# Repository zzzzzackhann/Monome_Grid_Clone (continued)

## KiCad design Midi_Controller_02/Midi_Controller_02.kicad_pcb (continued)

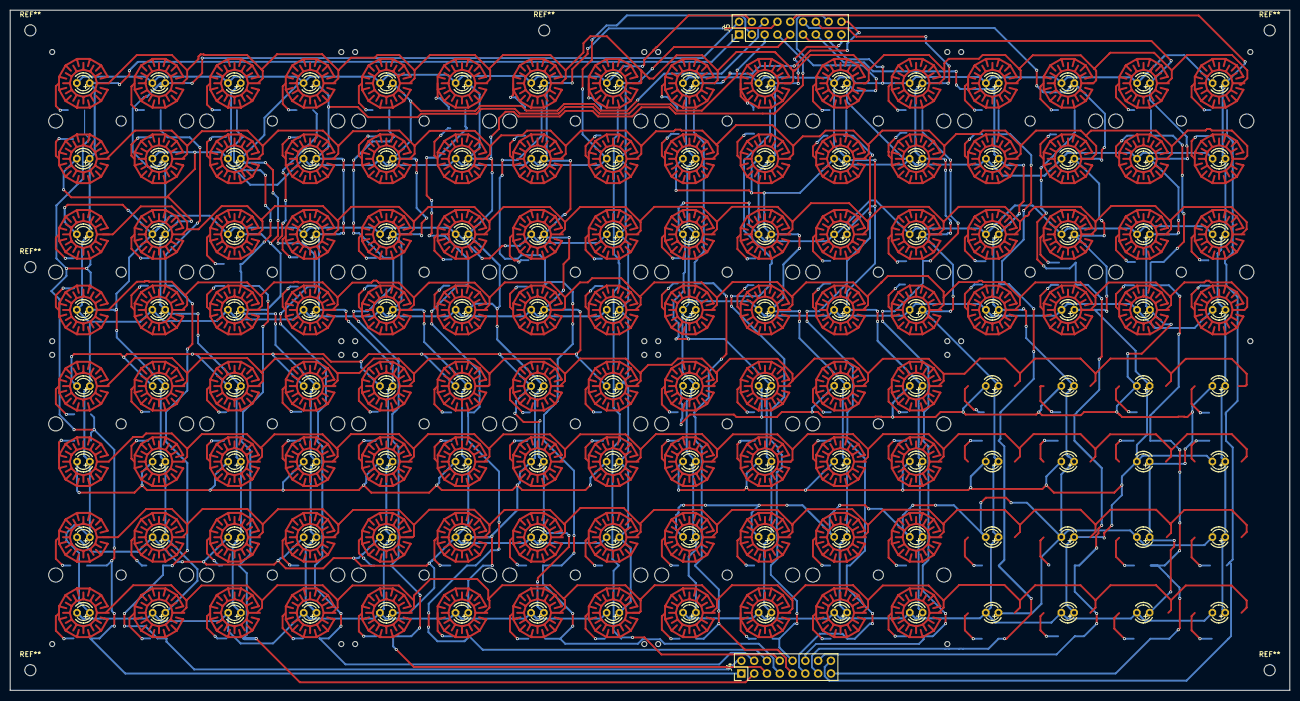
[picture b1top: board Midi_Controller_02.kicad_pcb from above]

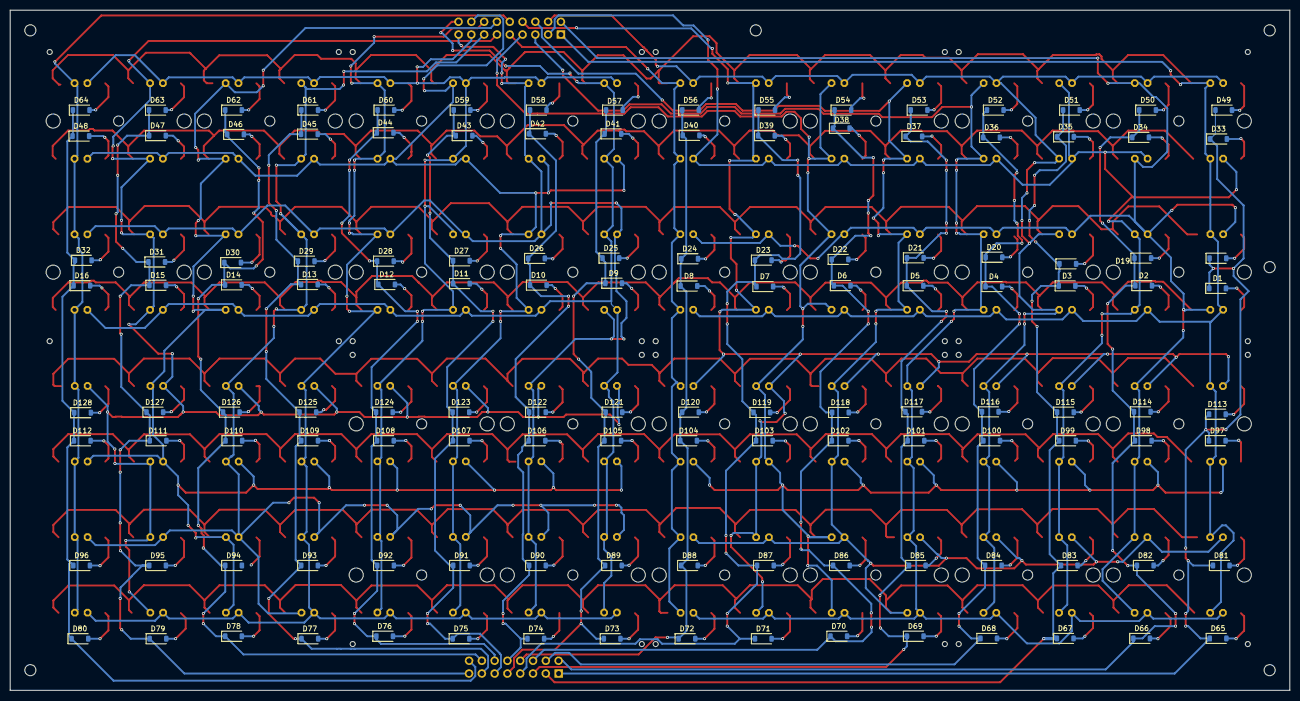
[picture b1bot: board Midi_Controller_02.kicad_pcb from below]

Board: 2 copper layers, 254.0 x 135.0 mm, 145 parts (128 on the bottom side), 154 nets.

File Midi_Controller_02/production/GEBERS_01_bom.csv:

Designator,Footprint,Quantity,Value,LCSC Part #
"D1, D10, D100, D101, D102, D103, D104, D105, D106, D107, D108, D109, D11, D110, D111, D112, D113, D114, D115, D116, D117, D118, D119, D12, D120, D121, D122, D123, D124, D125, D126, D127, D128, D13, D14, D15, D16, D17, D18, D19, D2, D20, D21, D22, D23, D24, D25, D26, D27, D28, D29, D3, D30, D31, D32, D33, D34, D35, D36, D37, D38, D39, D4, D40, D41, D42, D43, D44, D45, D46, D47, D48, D49, D5, D50, D51, D52, D53, D54, D55, D56, D57, D58, D59, D6, D60, D61, D62, D63, D64, D65, D66, D67, D68, D69, D7, D70, D71, D72, D73, D74, D75, D76, D77, D78, D79, D8, D80, D81, D82, D83, D84, D85, D86, D87, D88, D89, D9, D90, D91, D92, D93, D94, D95, D96, D97, D98, D99",D_SOD-123,128,1N4148,
J4,PinHeader_2x08_P2.54mm_Vertical,1,COL HEADER,
J5,PinHeader_2x09_P2.54mm_Vertical,1,CA HEADER,
"LED1, LED2, LED3, LED4, LED5, LED6, LED7, LED8",LED3MM-4X4GRID,8,~,
"SW2, SW3, SW4, SW5, SW6, SW7, SW8, SW9",ELAST_PAD_SQUARE_10MM_5.4MM_4X4GRID,8,~,

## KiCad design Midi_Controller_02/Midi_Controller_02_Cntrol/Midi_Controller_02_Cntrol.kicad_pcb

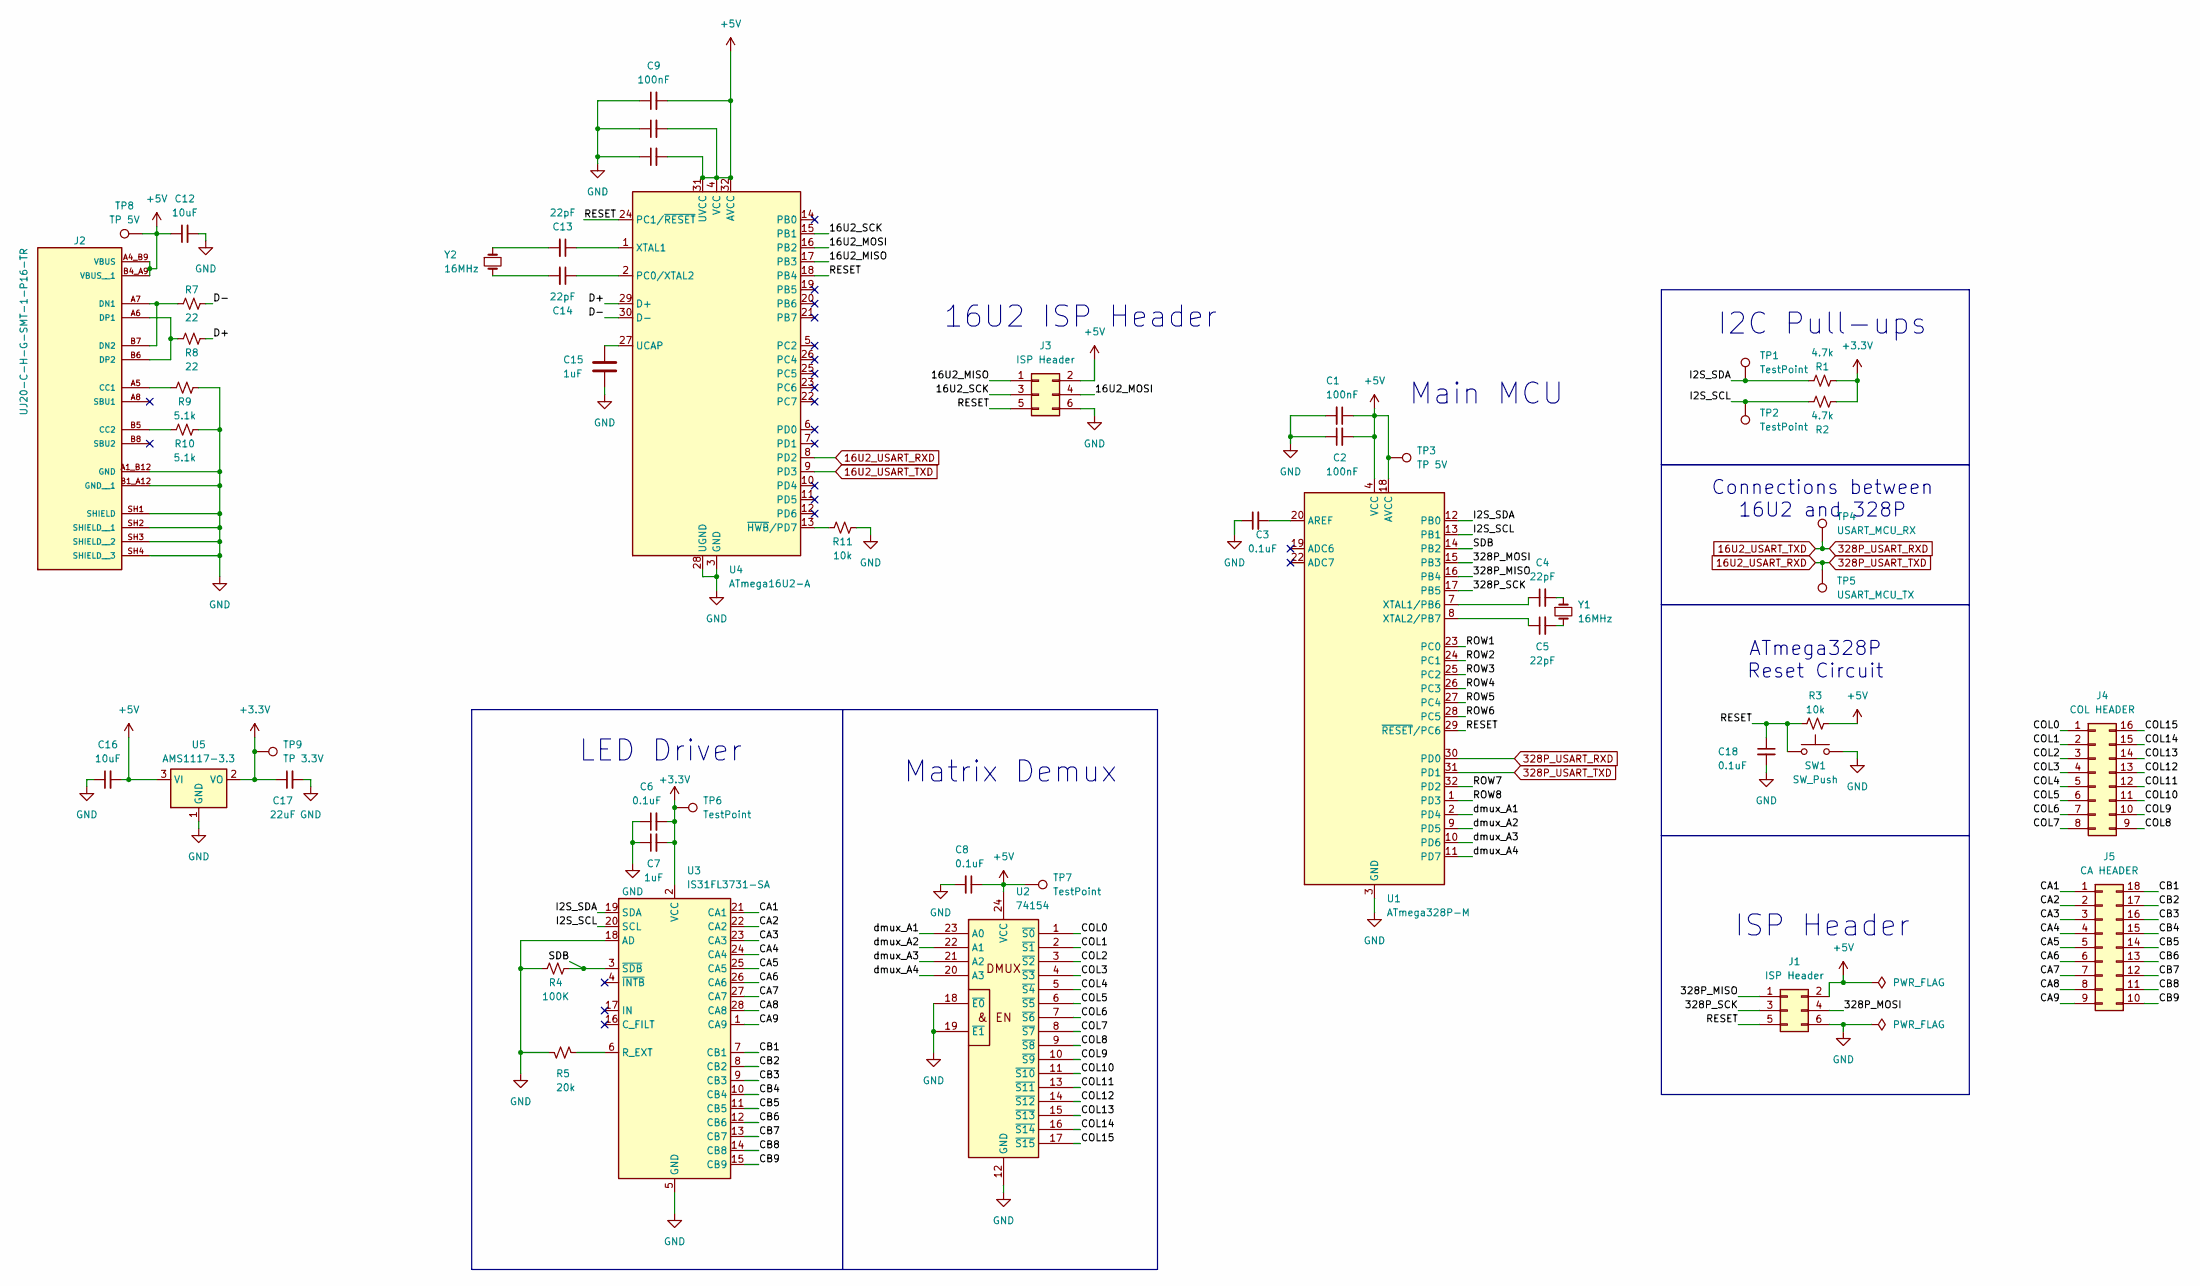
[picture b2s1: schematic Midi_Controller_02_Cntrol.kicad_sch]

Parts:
C1, C2, C9, C10, C11: 100nF; C_0805_2012Metric
C3, C6, C8, C18: 0.1uF; C_0805_2012Metric
C4, C5, C13, C14: 22pF; C_0805_2012Metric
C7, C15: 1uF; C_0805_2012Metric
C12, C16: 10uF; C_0805_2012Metric
C17: 22uF; C_0805_2012Metric
J1, J3: ISP Header; TestPoint_Pad_D1.0mm_2x3
J2: UJ20-C-H-G-SMT-1-P16-TR; SAMESKY_UJ20-C-H-G-SMT-1-P16-TR; PARTREV 1.0
J4: COL HEADER; PinHeader_2x08_P2.54mm_Horizontal
J5: CA HEADER; PinHeader_2x09_P2.54mm_Horizontal
R1, R2: 4.7k; R_0805_2012Metric
R3, R11: 10k; R_0805_2012Metric
R4: 100K; R_0805_2012Metric
R5: 20k; R_0805_2012Metric
R7, R8: 22; R_0805_2012Metric
R9, R10: 5.1k; R_0805_2012Metric
SW1: SW_Push; SW_TS04-66-55-BK-100-SMT
TP1, TP2: TestPoint; SolderWire-0.5sqmm_1x01_D0.9mm_OD2.3mm
TP3, TP8: TP 5V; TestPoint_Pad_D1.5mm
TP4: USART_MCU_RX; SolderWire-0.5sqmm_1x01_D0.9mm_OD2.3mm
TP5: USART_MCU_TX; SolderWire-0.5sqmm_1x01_D0.9mm_OD2.3mm
TP6, TP7: TestPoint; TestPoint_Pad_D1.5mm
TP9: TP 3.3V; TestPoint_Pad_D1.5mm
U1: ATmega328P-M; QFN-32-1EP_5x5mm_P0.5mm_EP3.1x3.1mm
U2: 74154; SOIC-24W_7.5x15.4mm_P1.27mm
U3: IS31FL3731-SA; SSOP-28_5.3x10.2mm_P0.65mm
U4: ATmega16U2-A; TQFP-32_7x7mm_P0.8mm
U5: AMS1117-3.3; SOT-223-3_TabPin2
Y1, Y2: 16MHz; Crystal_HC49-4H_Vertical

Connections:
16U2_USART_RXD: TP5.1 (1_1), U1.31 (PD1), U4.8 (PD2)
16U2_USART_TXD: TP4.1 (1_1), U1.30 (PD0), U4.9 (PD3)
+3.3V: C6.2, C7.2, C17.1, R1.1, R2.1, TP6.1 (1_1), TP9.1 (1_1), U3.2 (VCC), U5.2 (VO)
+5V: C1.1, C2.2, C8.1, C9.2, C10.2, C11.2, C12.1, C16.2, J1.2, J2.A4_B9 (VBUS), J2.B4_A9 (VBUS__1), J3.2, R3.2, TP3.1 (1_1), TP7.1 (1_1), TP8.1 (1_1), U1.4 (VCC), U1.6 (VCC), U1.18 (AVCC), U2.24 (VCC), U4.4 (VCC), U4.31 (UVCC), U4.32 (AVCC), U5.3 (VI)
/16U2_MISO: J3.1, U4.17 (PB3)
/16U2_MOSI: J3.4, U4.16 (PB2)
/16U2_SCK: J3.3, U4.15 (PB1)
/328P_MISO: J1.1, U1.16 (PB4)
/328P_MOSI: J1.4, U1.15 (PB3)
/328P_SCK: J1.3, U1.17 (PB5)
/CA1: J5.1, U3.21 (CA1)
/CA2: J5.2, U3.22 (CA2)
/CA3: J5.3, U3.23 (CA3)
/CA4: J5.4, U3.24 (CA4)
/CA5: J5.5, U3.25 (CA5)
/CA6: J5.6, U3.26 (CA6)
/CA7: J5.7, U3.27 (CA7)
/CA8: J5.8, U3.28 (CA8)
/CA9: J5.9, U3.1 (CA9)
/CB1: J5.18, U3.7 (CB1)
/CB2: J5.17, U3.8 (CB2)
/CB3: J5.16, U3.9 (CB3)
/CB4: J5.15, U3.10 (CB4)
/CB5: J5.14, U3.11 (CB5)
/CB6: J5.13, U3.12 (CB6)
/CB7: J5.12, U3.13 (CB7)
/CB8: J5.11, U3.14 (CB8)
/CB9: J5.10, U3.15 (CB9)
/COL0: J4.1, U2.1 (~S0)
/COL1: J4.2, U2.2 (~S1)
/COL2: J4.3, U2.3 (~S2)
/COL3: J4.4, U2.4 (~S3)
/COL4: J4.5, U2.5 (~S4)
/COL5: J4.6, U2.6 (~S5)
/COL6: J4.7, U2.7 (~S6)
/COL7: J4.8, U2.8 (~S7)
/COL8: J4.9, U2.9 (~S8)
/COL9: J4.10, U2.10 (~S9)
/COL10: J4.11, U2.11 (~S10)
/COL11: J4.12, U2.13 (~S11)
/COL12: J4.13, U2.14 (~S12)
/COL13: J4.14, U2.15 (~S13)
/COL14: J4.15, U2.16 (~S14)
/COL15: J4.16, U2.17 (~S15)
/D+: R8.1, U4.29 (D+)
/D-: R7.2, U4.30 (D-)
/I2S_SCL: R2.2, TP2.1 (1_1), U1.13 (PB1), U3.20 (SCL)
/I2S_SDA: R1.2, TP1.1 (1_1), U1.12 (PB0), U3.19 (SDA)
/RESET: C18.1, J1.5, J3.5, R3.1, SW1.1, U1.29 (~RESET/PC6), U4.18 (PB4), U4.24 (PC1/~RESET)
/ROW1: U1.23 (PC0)
/ROW2: U1.24 (PC1)
/ROW3: U1.25 (PC2)
/ROW4: U1.26 (PC3)
/ROW5: U1.27 (PC4)
/ROW6: U1.28 (PC5)
/ROW7: U1.32 (PD2)
/ROW8: U1.1 (PD3)
/SDB: R4.2, U1.14 (PB2), U3.3 (~SDB)
/dmux_A1: U1.2 (PD4), U2.23 (A0)
/dmux_A2: U1.9 (PD5), U2.22 (A1)
/dmux_A3: U1.10 (PD6), U2.21 (A2)
/dmux_A4: U1.11 (PD7), U2.20 (A3)
GND: C1.2, C2.1, C3.1, C6.1, C7.1, C8.2, C9.1, C10.1, C11.1, C12.2, C15.2, C16.1, C17.2, C18.2, J1.6, J2.A1_B12 (GND), J2.B1_A12 (GND__1), J2.SH1 (SHIELD), J2.SH2 (SHIELD__1), J2.SH3 (SHIELD__2), J2.SH4 (SHIELD__3), J3.6, R4.1, R5.1, R9.2, R10.1, R11.1, SW1.2, U1.3 (GND), U1.5 (GND), U1.21 (GND), U1.33 (GND), U2.12 (GND), U2.18 (~E0), U2.19 (~E1), U3.5 (GND), U3.18 (AD), U4.3 (GND), U4.28 (UGND), U5.1 (GND)
unnamed: C4.2, Y1.1
unnamed: C5.2, Y1.2
unnamed: C13.2, Y2.1
unnamed: C14.2, Y2.2
unnamed: J2.A5 (CC1), R9.1
unnamed: J2.B5 (CC2), R10.2
unnamed: J2.A7 (DN1), J2.B7 (DN2), R7.1
unnamed: J2.A6 (DP1), J2.B6 (DP2), R8.2
unnamed: C3.2, U1.20 (AREF)
unnamed: C4.1, U1.7 (XTAL1/PB6)
unnamed: C5.1, U1.8 (XTAL2/PB7)
unnamed: R5.2, U3.6 (R_EXT)
unnamed: C14.1, U4.2 (PC0/XTAL2)
unnamed: C15.1, U4.27 (UCAP)
unnamed: C13.1, U4.1 (XTAL1)
unnamed: R11.2, U4.13 (~HWB/PD7)

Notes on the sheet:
Main MCU
LED Driver
ISP Header
I2C Pull-ups
Connections between 16U2 and 328P
ATmega328P Reset Circuit
16U2 ISP Header
Matrix Demux

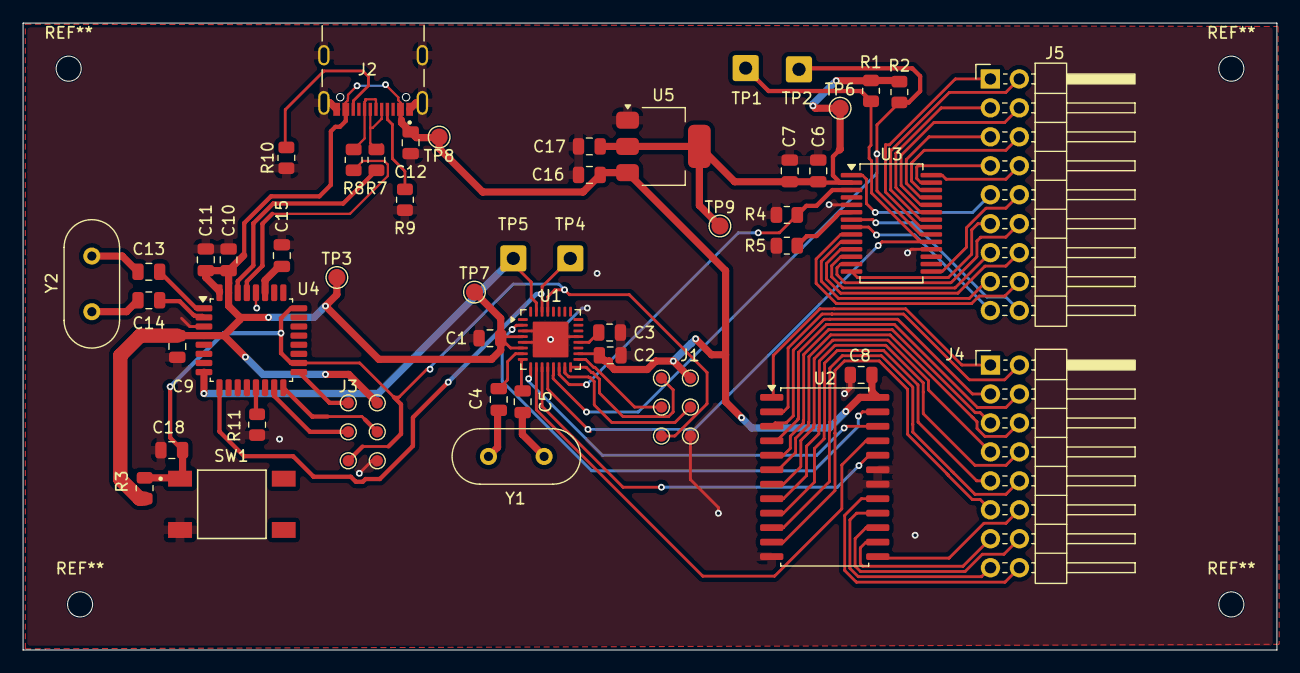
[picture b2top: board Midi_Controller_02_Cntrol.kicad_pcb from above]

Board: 2 copper layers, 110.0 x 55.0 mm, 50 parts (0 on the bottom side), 71 nets.

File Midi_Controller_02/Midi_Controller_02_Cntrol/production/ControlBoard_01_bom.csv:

Designator,Footprint,Quantity,Value,LCSC Part #
"C1, C10, C11, C2, C9",0805,5,100nF,
"C12, C16",0805,2,10uF,
"C13, C14, C4, C5",0805,4,22pF,
"C15, C7",0805,2,1uF,
C17,0805,1,20uF,
"C18, C3, C6, C8",0805,4,0.1uF,
"J1, J3",TestPoint_Pad_D1.0mm_2x3,2,ISP Header,
J2,SAMESKY_UJ20-C-H-G-SMT-1-P16-TR,1,UJ20-C-H-G-SMT-1-P16-TR,
J4,PinHeader_2x08_P2.54mm_Horizontal,1,COL HEADER,
J5,PinHeader_2x09_P2.54mm_Horizontal,1,CA HEADER,
"R1, R2",0805,2,4.7k,
"R10, R9",0805,2,5.1k,
"R11, R3",0805,2,10k,
R4,0805,1,100K,
R5,0805,1,20k,
"R7, R8",0805,2,22,
SW1,SW_TS04-66-55-BK-100-SMT,1,SW_Push,
"TP1, TP2",SolderWire-0.5sqmm_1x01_D0.9mm_OD2.3mm,2,TestPoint,
"TP3, TP8",TestPoint_Pad_D1.5mm,2,TP 5V,
TP4,SolderWire-0.5sqmm_1x01_D0.9mm_OD2.3mm,1,USART_MCU_RX,
TP5,SolderWire-0.5sqmm_1x01_D0.9mm_OD2.3mm,1,USART_MCU_TX,
"TP6, TP7",TestPoint_Pad_D1.5mm,2,TestPoint,
TP9,TestPoint_Pad_D1.5mm,1,TP 3.3V,
U1,QFN-32-1EP_5x5mm_P0.5mm_EP3.1x3.1mm,1,ATmega328P-M,
U2,SOIC-24W_7.5x15.4mm_P1.27mm,1,74154,
U3,SSOP-28_5.3x10.2mm_P0.65mm,1,IS31FL3731-SA,
U4,TQFP-32_7x7mm_P0.8mm,1,ATmega16U2-A,
U5,SOT-223-3_TabPin2,1,AMS1117-3.3,
"Y1, Y2",Crystal_HC49-4H_Vertical,2,16MHz,

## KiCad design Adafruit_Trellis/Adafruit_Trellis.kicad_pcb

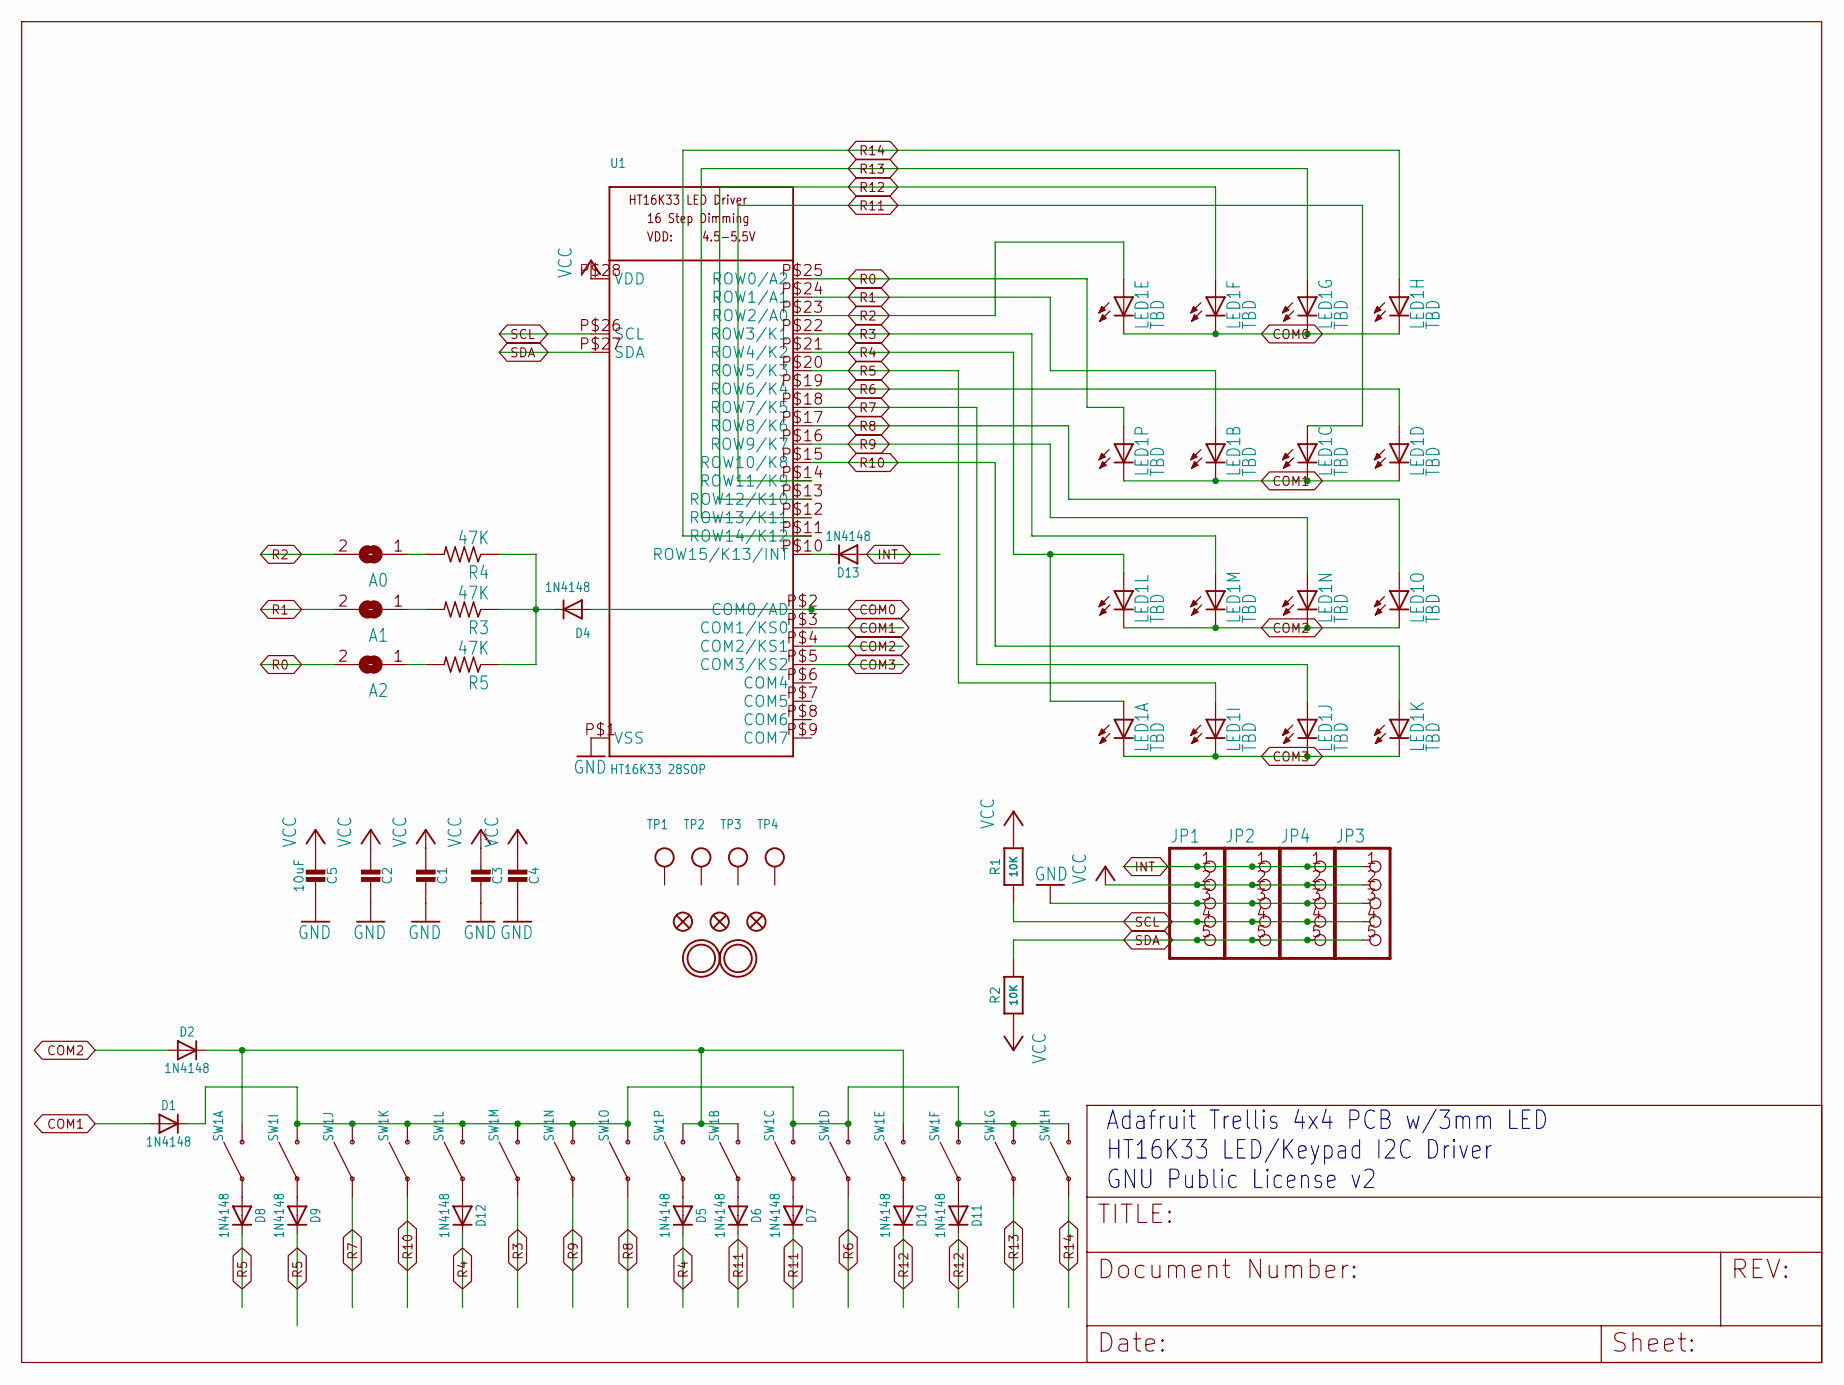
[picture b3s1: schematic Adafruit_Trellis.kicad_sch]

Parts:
A0, A1, A2: SOLDERJUMPERREFLOW_NOPASTE; SOLDERJUMPER_REFLOW_NOPASTE
C1, C2, C3, C4: CAP_CERAMIC_0805; _0805
C5: 10uF; _0805
D1, D2, D5, D6, D7, D8, D9, D10, D11, D12, D13: 1N4148; SOD-323
D4: 1N4148; SOD-323F
FID1, FID2, FID3: FIDUCIAL""; FIDUCIAL_1MM
JP1, JP2, JP3, JP4: HEADER-1X5EDGESMT; 1X5_SMT
LED1: TBD; LED3MM-4X4GRID
R1, R2: 10K; _0805
R3, R4, R5: 47K; R0805
SW1: SWITCH-SILICON-4X4GRID-10MM-5.4MM; ELAST_PAD_SQUARE_10MM_5.4MM_4X4GRID
TP1, TP2, TP3, TP4: TESTPOINT; TESTPOINT_SMT
U1: HT16K33 28SOP; SOP28_300MIL
U$1, U$2: MOUNTINGHOLE2.5; MOUNTINGHOLE_2.5_PLATED

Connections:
COM0: D4.A, LED1.K13 (C), LED1.K14 (C), LED1.K15 (C), LED1.K16 (C), U1.P$2 (COM0/AD)
COM1: D1.A, LED1.K9 (C), LED1.K10 (C), LED1.K11 (C), LED1.K12 (C), U1.P$3 (COM1/KS0)
COM2: D2.A, LED1.K5 (C), LED1.K6 (C), LED1.K7 (C), LED1.K8 (C), U1.P$4 (COM2/KS1)
COM3: LED1.K1 (C), LED1.K2 (C), LED1.K3 (C), LED1.K4 (C), U1.P$5 (COM3/KS2)
GND: C1.1, C2.1, C3.1, C4.1, C5.1, JP1.3, JP2.3, JP3.3, JP4.3, U1.P$1 (VSS)
INT: D13.A, JP1.1, JP2.1, JP3.1, JP4.1
unnamed: D2.C, SW1.B1, SW1.B9, SW1.B10, SW1.B13
unnamed: D13.C, U1.P$10 (ROW15/K13/INT)
unnamed: D5.A, SW1.A9
unnamed: D6.A, SW1.A10
unnamed: D1.C, SW1.B2, SW1.B3, SW1.B4, SW1.B5, SW1.B6, SW1.B7, SW1.B8, SW1.B11, SW1.B12, SW1.B14, SW1.B15, SW1.B16
unnamed: D7.A, SW1.A11
unnamed: D8.A, SW1.A1
unnamed: D9.A, SW1.A2
unnamed: A2.1, R5.2
unnamed: D10.A, SW1.A13
unnamed: D11.A, SW1.A14
unnamed: D12.A, SW1.A5
unnamed: D4.C, R3.1, R4.1, R5.1
unnamed: A1.1, R3.2
unnamed: A0.1, R4.2
R0: A2.2, LED1.A9 (A), U1.P$25 (ROW0/A2)
R1: A1.2, LED1.A10 (A), U1.P$24 (ROW1/A1)
R2: A0.2, LED1.A13 (A), U1.P$23 (ROW2/A0)
R3: LED1.A6 (A), SW1.A6, U1.P$22 (ROW3/K1)
R4: D5.C, D12.C, LED1.A1 (A), LED1.A5 (A), U1.P$21 (ROW4/K2)
R5: D8.C, D9.C, LED1.A2 (A), U1.P$20 (ROW5/K3)
R6: LED1.A12 (A), SW1.A12, U1.P$19 (ROW6/K4)
R7: LED1.A3 (A), SW1.A3, U1.P$18 (ROW7/K5)
R8: LED1.A8 (A), SW1.A8, U1.P$17 (ROW8/K6)
R9: LED1.A7 (A), SW1.A7, U1.P$16 (ROW9/K7)
R10: LED1.A4 (A), SW1.A4, U1.P$15 (ROW10/K8)
R11: D6.C, D7.C, LED1.A11 (A), U1.P$14 (ROW11/K9)
R12: D10.C, D11.C, LED1.A14 (A), U1.P$13 (ROW12/K10)
R13: LED1.A15 (A), SW1.A15, U1.P$12 (ROW13/K11)
R14: LED1.A16 (A), SW1.A16, U1.P$11 (ROW14/K12)
SCL: JP1.4, JP2.4, JP3.4, JP4.4, R1.1, U1.P$26 (SCL)
SDA: JP1.5, JP2.5, JP3.5, JP4.5, R2.2, U1.P$27 (SDA)
VCC: C1.2, C2.2, C3.2, C4.2, C5.2, JP1.2, JP2.2, JP3.2, JP4.2, R1.2, R2.1, U1.P$28 (VDD)

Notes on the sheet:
Adafruit Trellis 4x4 PCB w/3mm LED HT16K33 LED/Keypad I2C Driver GNU Public License v2

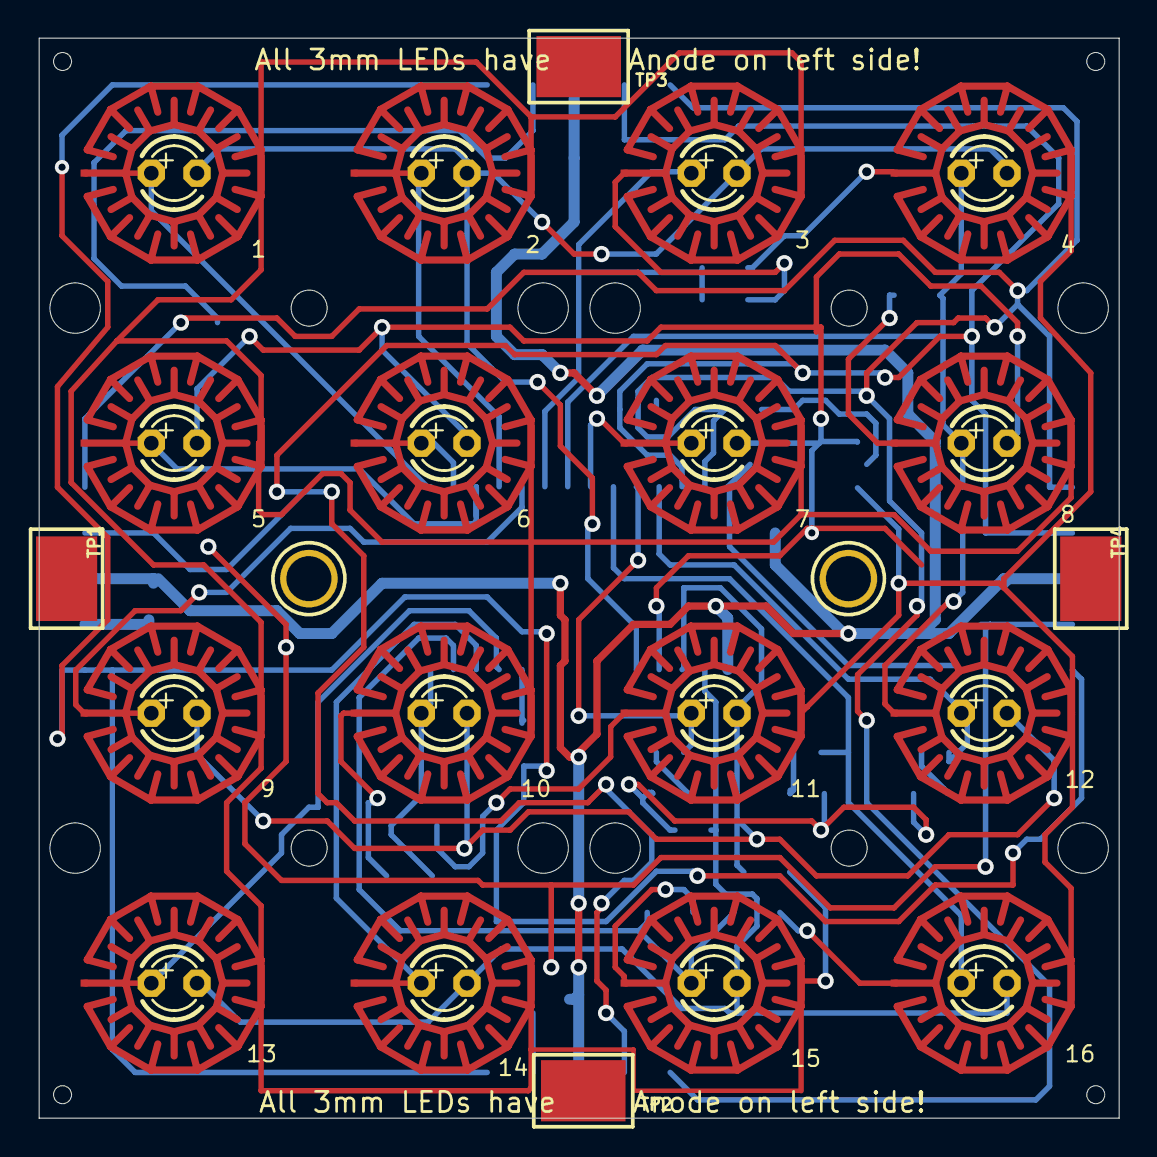
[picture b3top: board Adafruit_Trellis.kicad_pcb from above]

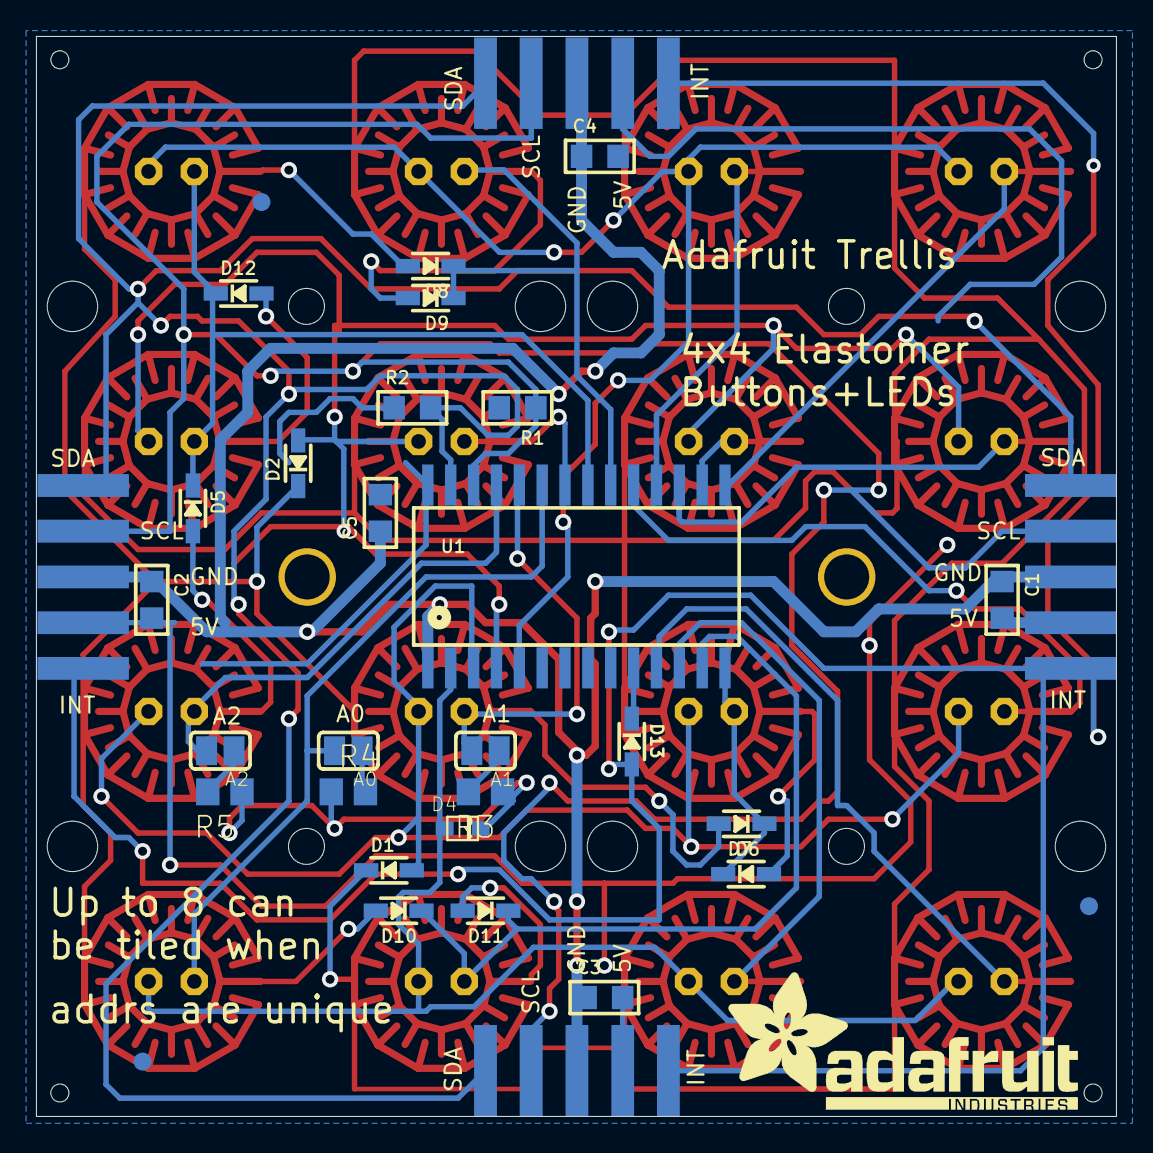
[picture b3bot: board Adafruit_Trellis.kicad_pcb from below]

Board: 2 copper layers, 60.0 x 60.0 mm, 42 parts (34 on the bottom side), 39 nets.

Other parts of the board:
U$3: ADAFRUIT_TEXT_20MM

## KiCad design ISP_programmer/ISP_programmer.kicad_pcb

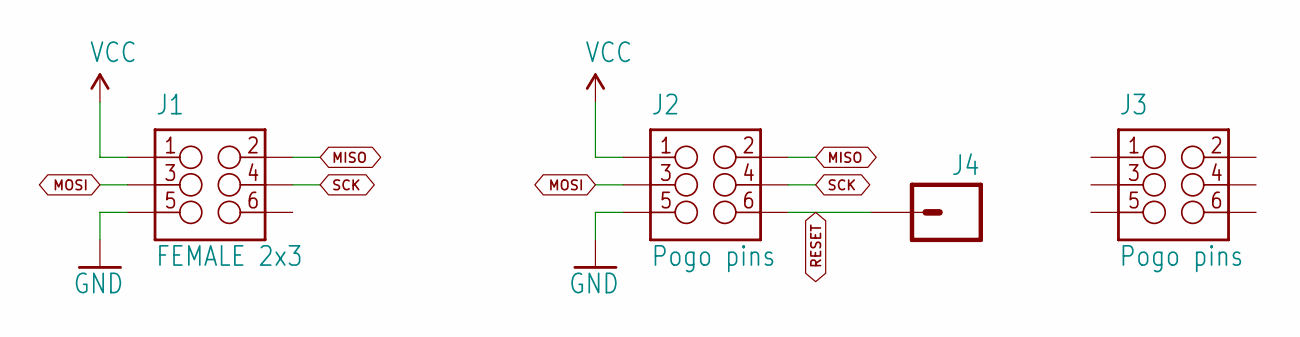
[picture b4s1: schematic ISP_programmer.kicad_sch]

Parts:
J1: FEMALE 2x3; 2X3
J2, J3: Pogo pins; 2X3_POGO
J4: M01PTH; 1X01

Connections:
GND: J1.5, J2.P$5 (5)
MISO: J1.2, J2.P$2 (2)
MOSI: J1.3, J2.P$3 (3)
RESET: J2.P$6 (6), J4.1
SCK: J1.4, J2.P$4 (4)
VCC: J1.1, J2.P$1 (1)

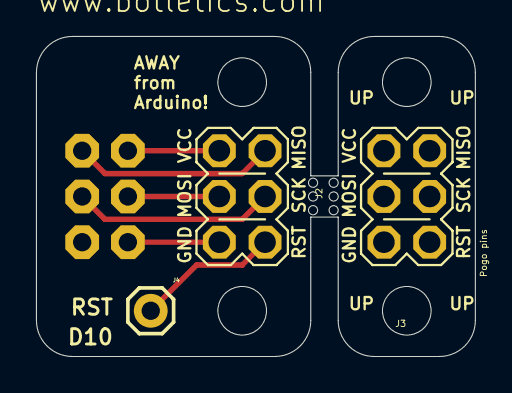
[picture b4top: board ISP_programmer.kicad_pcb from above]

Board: 2 copper layers, 24.4 x 17.8 mm, 14 parts (1 on the bottom side), 6 nets.

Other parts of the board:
UNK_HOLE_0: dummyfp0
UNK_HOLE_1: dummyfp1
UNK_HOLE_2: dummyfp2
UNK_HOLE_3: dummyfp3
UNK_HOLE_4: dummyfp4
UNK_HOLE_5: dummyfp5
UNK_HOLE_6: dummyfp6
UNK_HOLE_7: dummyfp7
UNK_HOLE_8: dummyfp8
UNK_HOLE_9: dummyfp9

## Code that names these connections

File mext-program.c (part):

/* On 328PB, RX is PD0 and TX and PD1 */
/* This is a test that stores data (chars) in a buffer of limited size (a ring buffer),
reads each byte and sends it back to the computer over uart. 
them one by one*/

/* I2C SDA is on PB0 and SCL is on PB1 */

#ifndef F_CPU
#define F_CPU 16000000UL
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So keep PORTBn at 0, so that whenever the DDRB is set to output it drives low, but then get's released when set to input. 
*/

#define I2C_SDA PB0
#define I2C_SCL PB1
#define I2C_DELAY_US 5

/* For LED driver */
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    return is31_write(IS31_PAGE_FUNCTION, IS31_REG_SHUTDOWN, 0x01);
}

#define DEMUX_A0 PD4
#define DEMUX_A1 PD5
#define DEMUX_A2 PD6
#define DEMUX_A3 PD7
#define DEMUX_MASK ((1 << DEMUX_A0) | (1 << DEMUX_A1) | (1 << DEMUX_A2) | (1 << DEMUX_A3))

#define ROWS_C_MASK ((1 << PC0) | (1 << PC1) | (1 << PC2) | (1 << PC3) | (1 << PC4) | (1 << PC5))
#define ROWS_D_MASK ((1 << PD2) | (1 << PD3))

#define GRID_COLS 16
#define GRID_ROWS 8
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
static volatile uint32_t ms_ticks = 0;

/* Button demux is on pins PD4, PD5, PD6, and PD7 */
static void demux_init(void) {
    DDRD |= DEMUX_MASK; // set 4 demux pins (A0-A3) as ouputs, default driven low
    
    DDRD &= ~ROWS_D_MASK; //turn PD2 and PD3 into inputs for Row 6 and Row 7 
    PORTD |= ROWS_D_MASK; // pull input pins high with internal pullup resistor
    DDRC &= ~ROWS_C_MASK; // input pins from Rows 0-5
    PORTC |= ((1 << PC0) | (1 << PC1) | (1 << PC2) | (1 << PC3) | (1 << PC4) | (1 << PC5)); // set pull up resistor
}

/* This is a sick technique for scanning through a fixed value in the registers*/
/* While row 1 is being held high by pull up resistors, the columns cycle through all of them.
If during any column check the pin goes low, it's because the button is pressed. */
static void demux_select(uint8_t column) {
    uint8_t d = PORTD & ~DEMUX_MASK; // keeps low four bits as they are and CLEARS four demux address bits (PD4-7)

    if (column & 0x01) d |= (1 << DEMUX_A0); // is bit 0 of the column number set? (true for columns 1, 3, 5 etc. )
    if (column & 0x02) d |= (1 << DEMUX_A1);
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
